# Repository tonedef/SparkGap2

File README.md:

# SparkGap2
This repo is for building the SparkGap2, a tube diode based overdrive guitar FX pedal, originally developed by Merlin Blencowe:
- [SparkGap2 design](https://valvewizard.co.uk/sparkgap.html)
- [Merlin's Website](https://www.valvewizard.co.uk/)
- [Merlin's Books](https://www.lulu.com/spotlight/valve_wizard)

v0.3 under releases is mostly tested and working with caveats. Still getting some noise that I'm debugging (like gain instead of clean pass-thru when the pedal is off). Latest version here is updated to fix those, but hasn't been fab'd yet to verify.

Feel free to contribute. Merlin's a great guy, and without a doubt in my mind the authority on valve designs. His books have taught me a lot not just about vacuum tube amplifiers and linear power supplies, but electronics in general. I can honestly say he's thourghly responsible for the thousands of dollars I've spent to become the proud owner of the tons of copper and glass that's currently occupying about a third of my garage and music studio in various forms of audio projects - the SparkGap2 will soon be among them. Thanks Merlin for your genius and all the fun it continues to bring!

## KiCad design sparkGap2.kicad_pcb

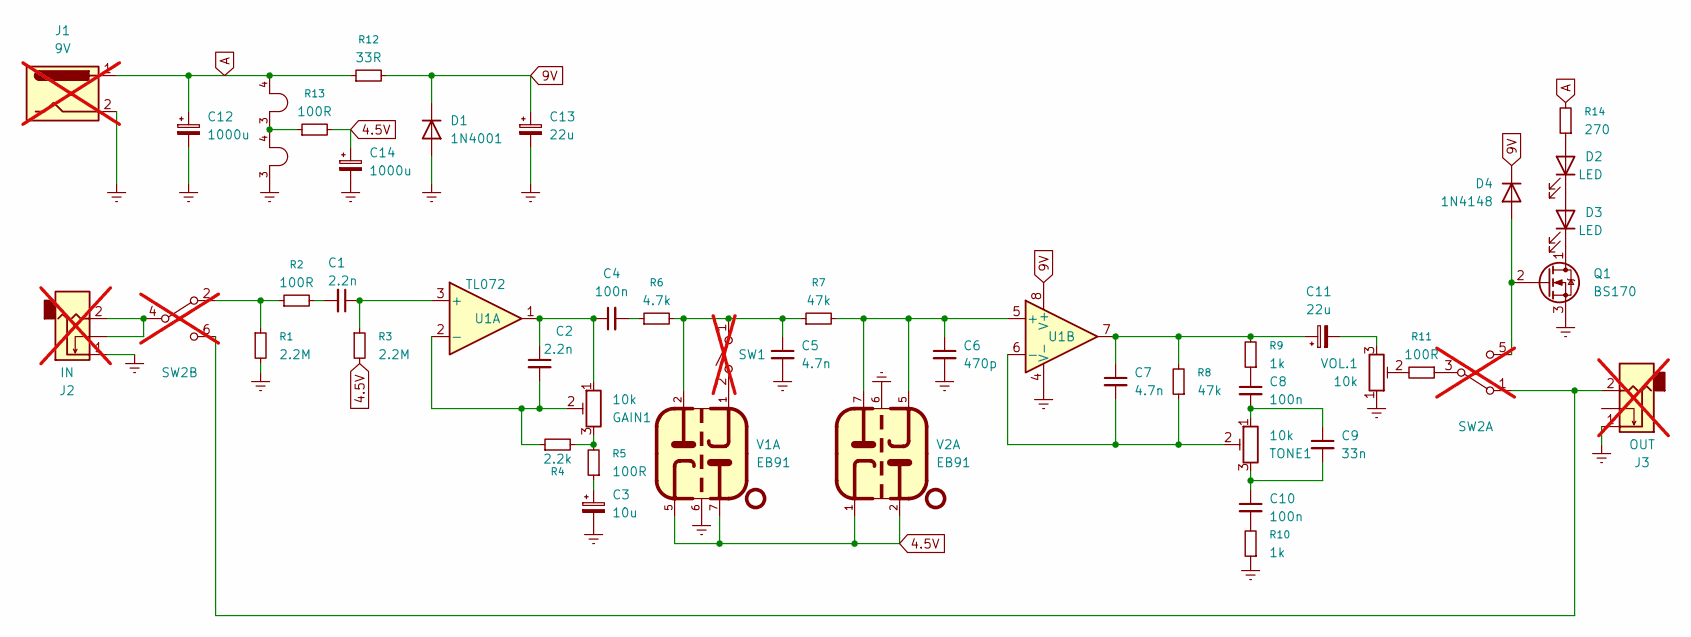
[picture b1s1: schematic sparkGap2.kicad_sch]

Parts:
C1, C2: 2.2n; C_Rect_L7.2mm_W2.5mm_P5.00mm_FKS2_FKP2_MKS2_MKP2; MFG Part B32529C1222K189
C3: 10u; CP_Radial_D5.0mm_P2.00mm; MFG Part EEU-FR1H100
C4, C8, C10: 100n; C_Rect_L7.2mm_W2.5mm_P5.00mm_FKS2_FKP2_MKS2_MKP2; MFG Part MKT1817410065
C5, C7: 4.7n; C_Rect_L7.2mm_W2.5mm_P5.00mm_FKS2_FKP2_MKS2_MKP2; MFG Part B32529C1472K000
C6: 470p; C_Rect_L7.2mm_W2.5mm_P5.00mm_FKS2_FKP2_MKS2_MKP2; MFG Part FKS2D004701A00JSSD
C9: 33n; C_Rect_L7.2mm_W2.5mm_P5.00mm_FKS2_FKP2_MKS2_MKP2; MFG Part B32529C0333K189
C11, C13: 22u; CP_Radial_D5.0mm_P2.00mm; MFG Part EEU-FR1H220
C12, C14: 1000u; CP_Radial_D10.0mm_P5.00mm; MFG Part 16PX1000MEFC10X12.5
D1: 1N4001; D_DO-41_SOD81_P2.54mm_Vertical_AnodeUp; MFG Part 1N4001RLG
D2, D3: LED; LED_D3.0mm; MFG Part BL-BJU3V1
D4: 1N4148; D_DO-35_SOD27_P2.54mm_Vertical_AnodeUp; MFG Part 1N4148-T50A
GAIN1: 10k; potentiometer_vert_no_switch; MFG Part RK09L1140A5L
J1: 9V; PinSocket_1x02_P2.54mm_Vertical; MFG Part 54-00151; not fitted
J2: IN; PinSocket_1x02_P2.54mm_Vertical; MFG Part NMJ4HC-S; not fitted
J3: OUT; PinSocket_1x02_P2.54mm_Vertical; MFG Part NMJ4HC-S; not fitted
Mount1, Mount2: B9A Mount; B9A-shield-single-mount; MFG Part 971100354
Q1: BS170; TO-92_Inline_Wide; MFG Part BS170
R1, R3: 2.2M; R_Axial_DIN0207_L6.3mm_D2.5mm_P2.54mm_Vertical
R2, R5, R11, R13: 100R; R_Axial_DIN0207_L6.3mm_D2.5mm_P2.54mm_Vertical
R4: 2.2k; R_Axial_DIN0207_L6.3mm_D2.5mm_P2.54mm_Vertical
R6: 4.7k; R_Axial_DIN0207_L6.3mm_D2.5mm_P2.54mm_Vertical
R7: 47k; R_Axial_DIN0207_L6.3mm_D2.5mm_P7.62mm_Horizontal
R8: 47k; R_Axial_DIN0207_L6.3mm_D2.5mm_P2.54mm_Vertical
R9, R10: 1k; R_Axial_DIN0207_L6.3mm_D2.5mm_P2.54mm_Vertical
R12: 33R; R_Axial_DIN0207_L6.3mm_D2.5mm_P2.54mm_Vertical
R14: 270; R_Axial_DIN0207_L6.3mm_D2.5mm_P2.54mm_Vertical
SW1: SPST; PinSocket_1x02_P2.54mm_Vertical; MFG Part SW-T3-1A-A-A3-S1; not fitted
SW2: 6-pin Footswitch; PinHeader_2x03_P2.54mm_Vertical; MFG Part SF12020DF; not fitted
TONE1: 10k; potentiometer_vert_no_switch; MFG Part RK09L1140A5L
U1: TL072; DIP-8_W7.62mm_LongPads; MFG Part TL072IP
V1, V2: EB91; B7G (7 Pin Mini)-B9A-shield-mount
VOL.1: 10k; potentiometer_vert_no_switch; MFG Part RK09L1140A5L

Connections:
4.5V: C14.1, R3.2, R13.2, V1.5, V1.7, V2.1, V2.2
9V: C13.1, D1.1 (K), D4.1 (K), R12.2, U1.8 (V+)
A: C12.1, J1.1, R12.1, R14.2, V1.4
Earth: C3.2, C5.2, C6.2, C12.2, C13.2, C14.2, D1.2 (A), J1.2, J2.1, J3.1, Q1.3 (S), R1.2, R10.1, U1.4 (V-), V1.6, V2.3, V2.6, VOL.1.1
unnamed: C1.2, R2.2
unnamed: C2.1, C4.1, GAIN1.1, U1.1
unnamed: C3.1, R5.1
unnamed: C4.2, R6.1
unnamed: C8.1, R9.1
unnamed: C8.2, C9.1, TONE1.1
unnamed: C9.2, C10.1, TONE1.3
unnamed: C10.2, R10.2
unnamed: C7.1, C11.1, R8.2, R9.2, U1.7
unnamed: C11.2, VOL.1.3
unnamed: D2.2 (A), R14.1
unnamed: D2.1 (K), D3.2 (A)
unnamed: D3.1 (K), Q1.1 (D)
unnamed: D4.2 (A), Q1.2 (G), SW2.5
unnamed: GAIN1.3, R4.2, R5.2
unnamed: J2.2, SW2.4
unnamed: J3.2, SW2.1, SW2.6
unnamed: R1.1, R2.1, SW2.2
unnamed: R11.1, SW2.3
unnamed: R11.2, VOL.1.2
unnamed: R13.1, V1.3, V2.4
unnamed: C5.1, R6.2, R7.1, SW1.1 (A), V1.2
unnamed: SW1.2 (B), V1.1
unnamed: C1.1, R3.1, U1.3 (+)
unnamed: C2.2, GAIN1.2, R4.1, U1.2 (-)
unnamed: C6.1, R7.2, U1.5 (+), V2.5, V2.7
unnamed: C7.2, R8.1, TONE1.2, U1.6 (-)

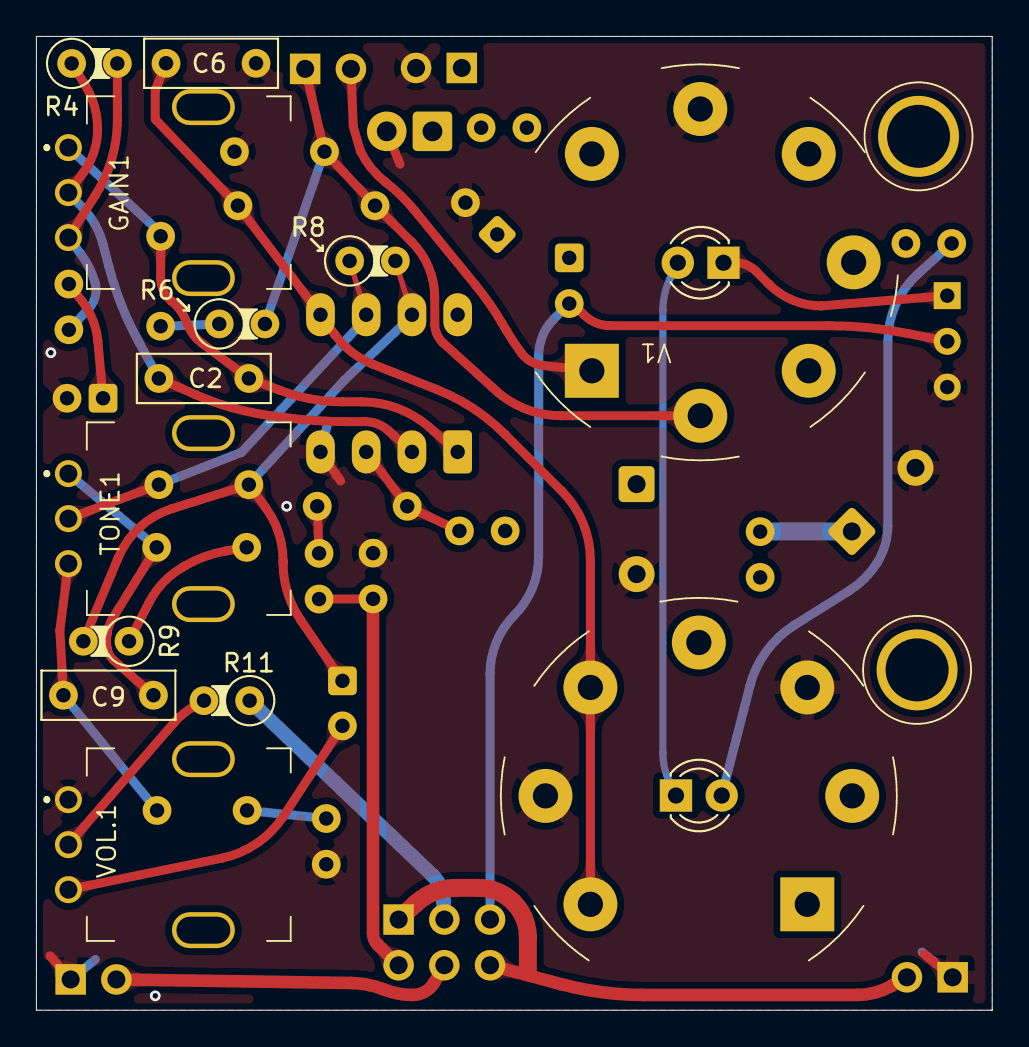
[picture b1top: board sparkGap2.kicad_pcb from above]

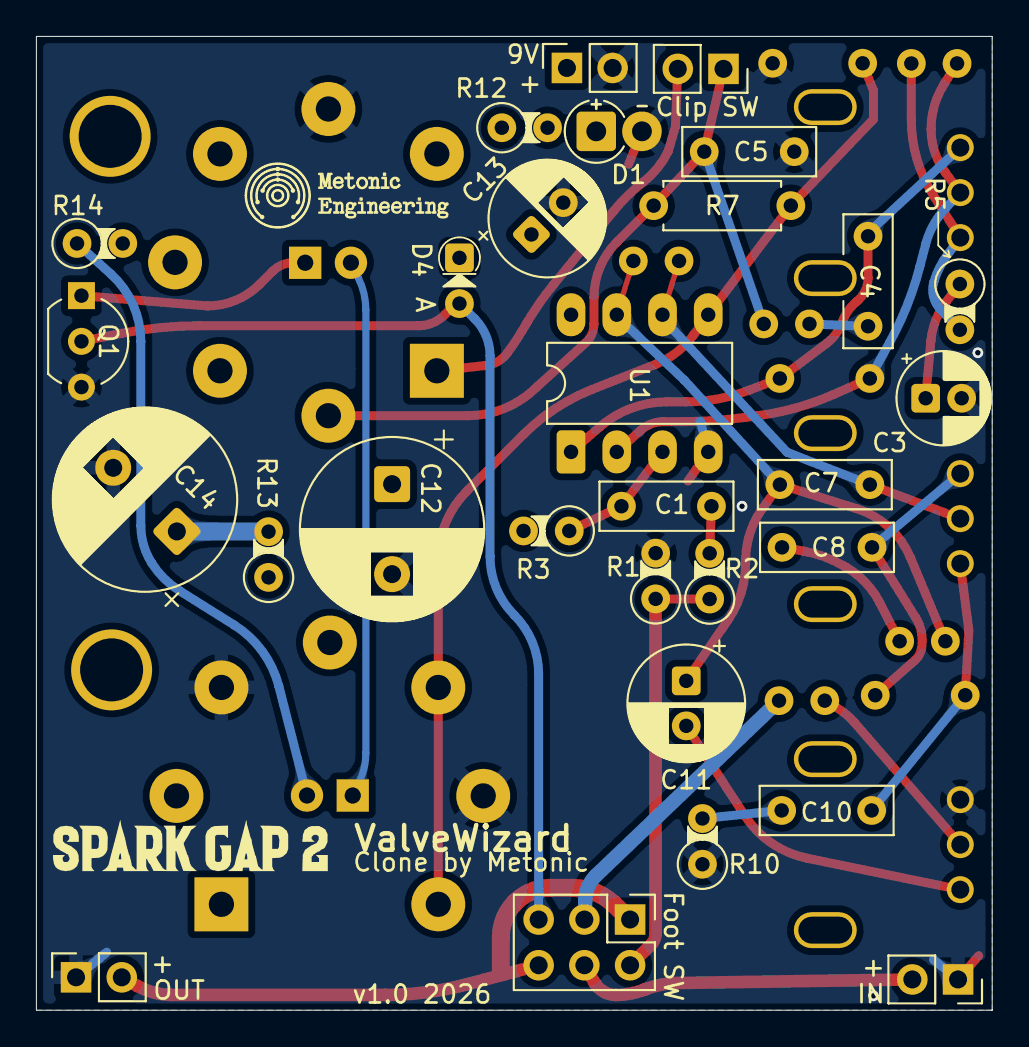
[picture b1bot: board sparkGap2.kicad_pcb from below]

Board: 4 copper layers, 53.1 x 54.1 mm, 46 parts (29 on the bottom side), 31 nets.

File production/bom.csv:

Designator,Footprint,Quantity,Value,LCSC Part #
"C1, C2",C_Rect_L7.2mm_W2.5mm_P5.00mm_FKS2_FKP2_MKS2_MKP2,2,2.2n,
"C10, C4, C8",C_Rect_L7.2mm_W2.5mm_P5.00mm_FKS2_FKP2_MKS2_MKP2,3,100n,
"C11, C13",CP_Radial_D6.3mm_P2.50mm,2,22u,
"C12, C14",CP_Radial_D10.0mm_P5.00mm,2,1000u,
C3,CP_Radial_D5.0mm_P2.00mm,1,10u,
"C5, C7",C_Rect_L7.2mm_W2.5mm_P5.00mm_FKS2_FKP2_MKS2_MKP2,2,4.7n,
C6,C_Rect_L7.2mm_W2.5mm_P5.00mm_FKS2_FKP2_MKS2_MKP2,1,470p,
C9,C_Rect_L7.2mm_W2.5mm_P5.00mm_FKS2_FKP2_MKS2_MKP2,1,33n,
D1,D_DO-41_SOD81_P2.54mm_Vertical_AnodeUp,1,1N4001,
"D2, D3",LED_D3.0mm,2,LED,
D4,D_DO-35_SOD27_P2.54mm_Vertical_AnodeUp,1,1N4148,
"GAIN1, TONE1, VOL.1",potentiometer_vert_no_switch,3,10k,
"MOUNT1, MOUNT2",B9A-shield-single-mount,2,B9A Mount,
Q1,TO-92_Inline_Wide,1,BS170,
"R1, R3",R_Axial_DIN0207_L6.3mm_D2.5mm_P2.54mm_Vertical,2,2.2M,
"R10, R14, R9",R_Axial_DIN0207_L6.3mm_D2.5mm_P2.54mm_Vertical,3,1k,
"R11, R13, R2, R5",R_Axial_DIN0207_L6.3mm_D2.5mm_P2.54mm_Vertical,4,100R,
R12,R_Axial_DIN0207_L6.3mm_D2.5mm_P2.54mm_Vertical,1,33R,
R4,R_Axial_DIN0207_L6.3mm_D2.5mm_P2.54mm_Vertical,1,2.2k,
R6,R_Axial_DIN0207_L6.3mm_D2.5mm_P2.54mm_Vertical,1,4.7k,
R7,R_Axial_DIN0207_L6.3mm_D2.5mm_P7.62mm_Horizontal,1,47k,
R8,R_Axial_DIN0207_L6.3mm_D2.5mm_P2.54mm_Vertical,1,47k,
U1,DIP-8_W7.62mm_LongPads,1,TL072,
"V1, V2",B7G (7 Pin Mini)-B9A-shield-mount,2,EB91,

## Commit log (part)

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2025-12-13 Fix image link for SparkGap2 PCB render
    Updated image link for SparkGap2 PCB render to use GitHub's blob URL format.
2026-01-07 Add missing current limit resistor
2026-01-07 Improve gnd routing and gfx
2026-01-25 add .gitignore
2026-01-25 correct version info
2026-01-28 Fix schematic errors. Renumber to match ValveWizard schematic. Improve layout. Switch to 4 layer
2026-01-28 updated img location
2026-01-28 additional txt
2026-01-29 Tweak PCB layout. Add enclosure drill template and GFX. Delete unused backups
2026-01-29 ignore backups folder
2026-02-02 move mount holes to 60 deg.
2026-03-15 Slight adjustments to layout. Clean up component numbering.
2026-04-14 add back mount holes
2026-04-16 bump ver.
2026-04-16 Address issues found with last production run
2026-04-16 add build guide, improve BOM, gen production
2026-04-16 Update build guide
2026-04-16 Build guide updates
2026-04-17 Update SVG, CNC files. Improve traces around pots
2026-04-17 Clarify v0.3 status and debugging notes in README
    Updated the README to clarify the status of v0.3 and ongoing debugging issues.
2026-04-17 Fix grammar and clarity in README.md
    Corrected minor grammatical errors and improved clarity.
2026-04-17 Clean up footprints and schematic to get rid of warnings
2026-04-17 Reduce carve depth. Increase feeds and speeds
2026-04-18 change feeds/speeds and V depth
2026-04-20 update to KiCad v10
2026-04-20 ignore "#auto" files
2026-04-25 Improve layout to aid in construction, better signal routing, and more visually appealing shield/PCB mounts
